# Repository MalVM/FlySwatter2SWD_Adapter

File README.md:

# FlySwatter2SWD_Adapter
An adapter for flyswatter 2 to SWD with trim pot as resistors

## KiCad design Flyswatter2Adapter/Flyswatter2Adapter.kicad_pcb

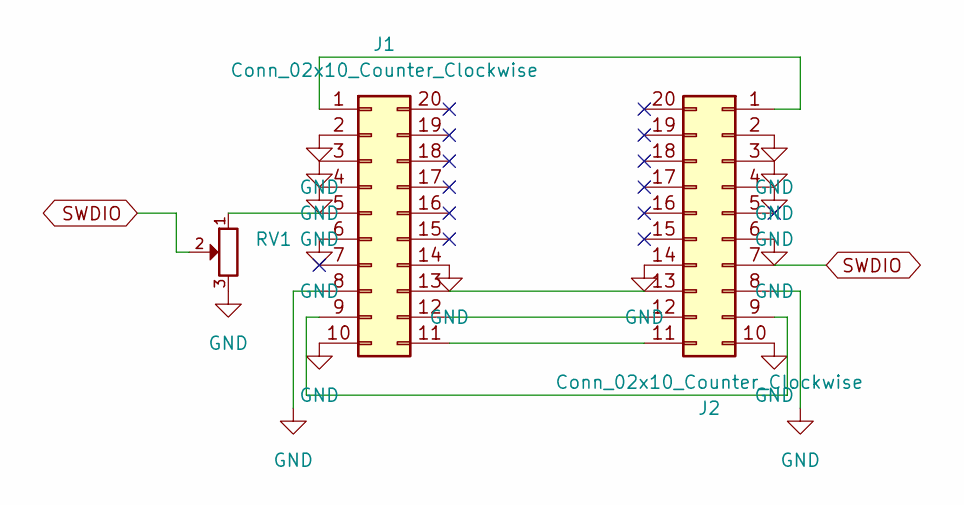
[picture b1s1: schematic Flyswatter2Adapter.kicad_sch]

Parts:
J1, J2: Conn_02x10_Counter_Clockwise; IDC-Header_2x10_P2.54mm_Latch6.5mm_Vertical
RV1: potentiometer_RM065; Potentiometer_RM065

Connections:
GND: J1.2, J1.3, J1.4, J1.6, J1.8, J1.10, J1.14, J2.2, J2.3, J2.4, J2.6, J2.8, J2.10, J2.14, RV1.3
unnamed: J1.1, J2.1
unnamed: J1.5, RV1.1
unnamed: J1.9, J2.9
unnamed: J1.11, J2.11
unnamed: J1.12, J2.12
unnamed: J1.13, J2.13
SWDIO: J2.7, RV1.2

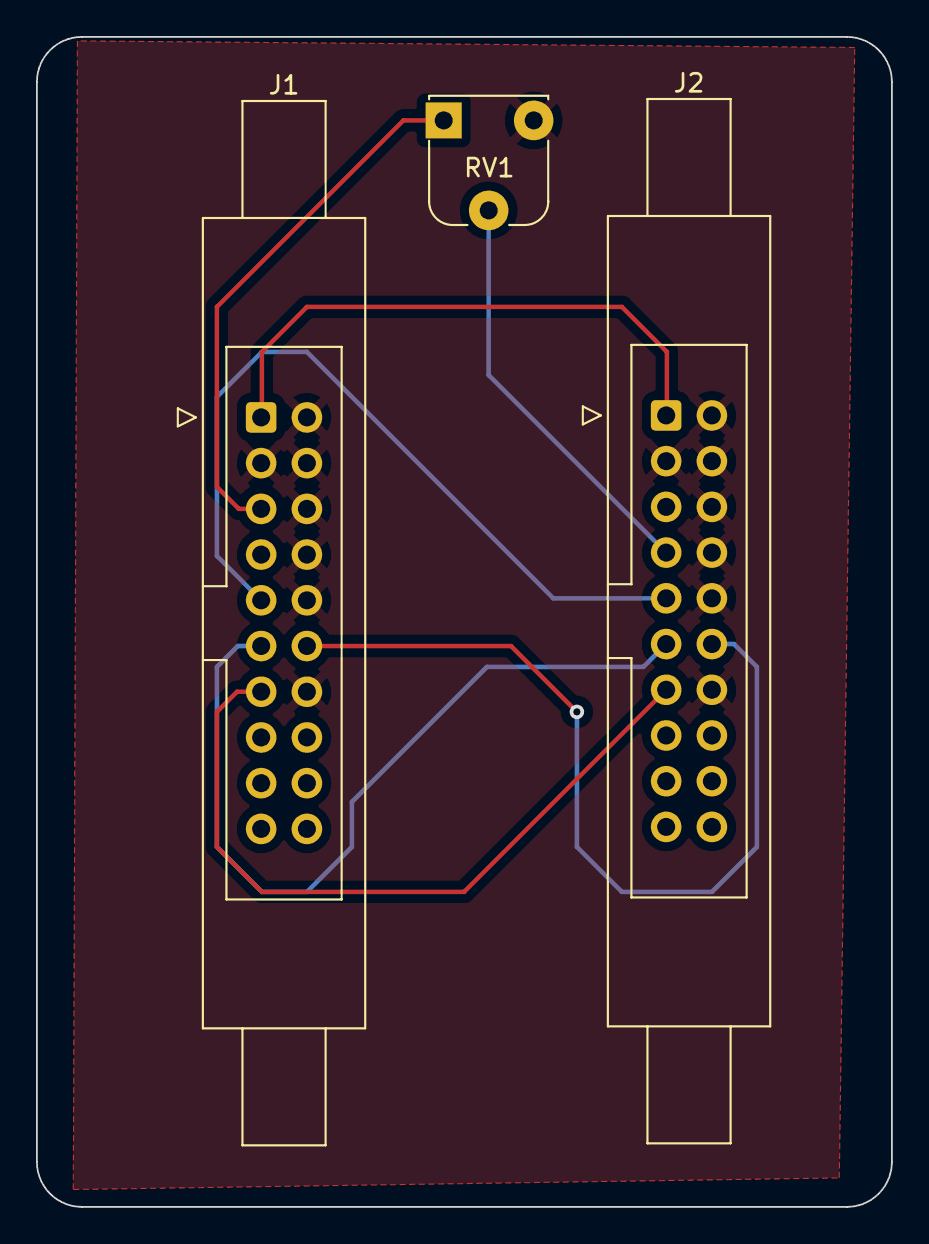
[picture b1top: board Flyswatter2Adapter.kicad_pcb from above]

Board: 4 copper layers, 47.5 x 65.0 mm, 3 parts (0 on the bottom side), 8 nets.
